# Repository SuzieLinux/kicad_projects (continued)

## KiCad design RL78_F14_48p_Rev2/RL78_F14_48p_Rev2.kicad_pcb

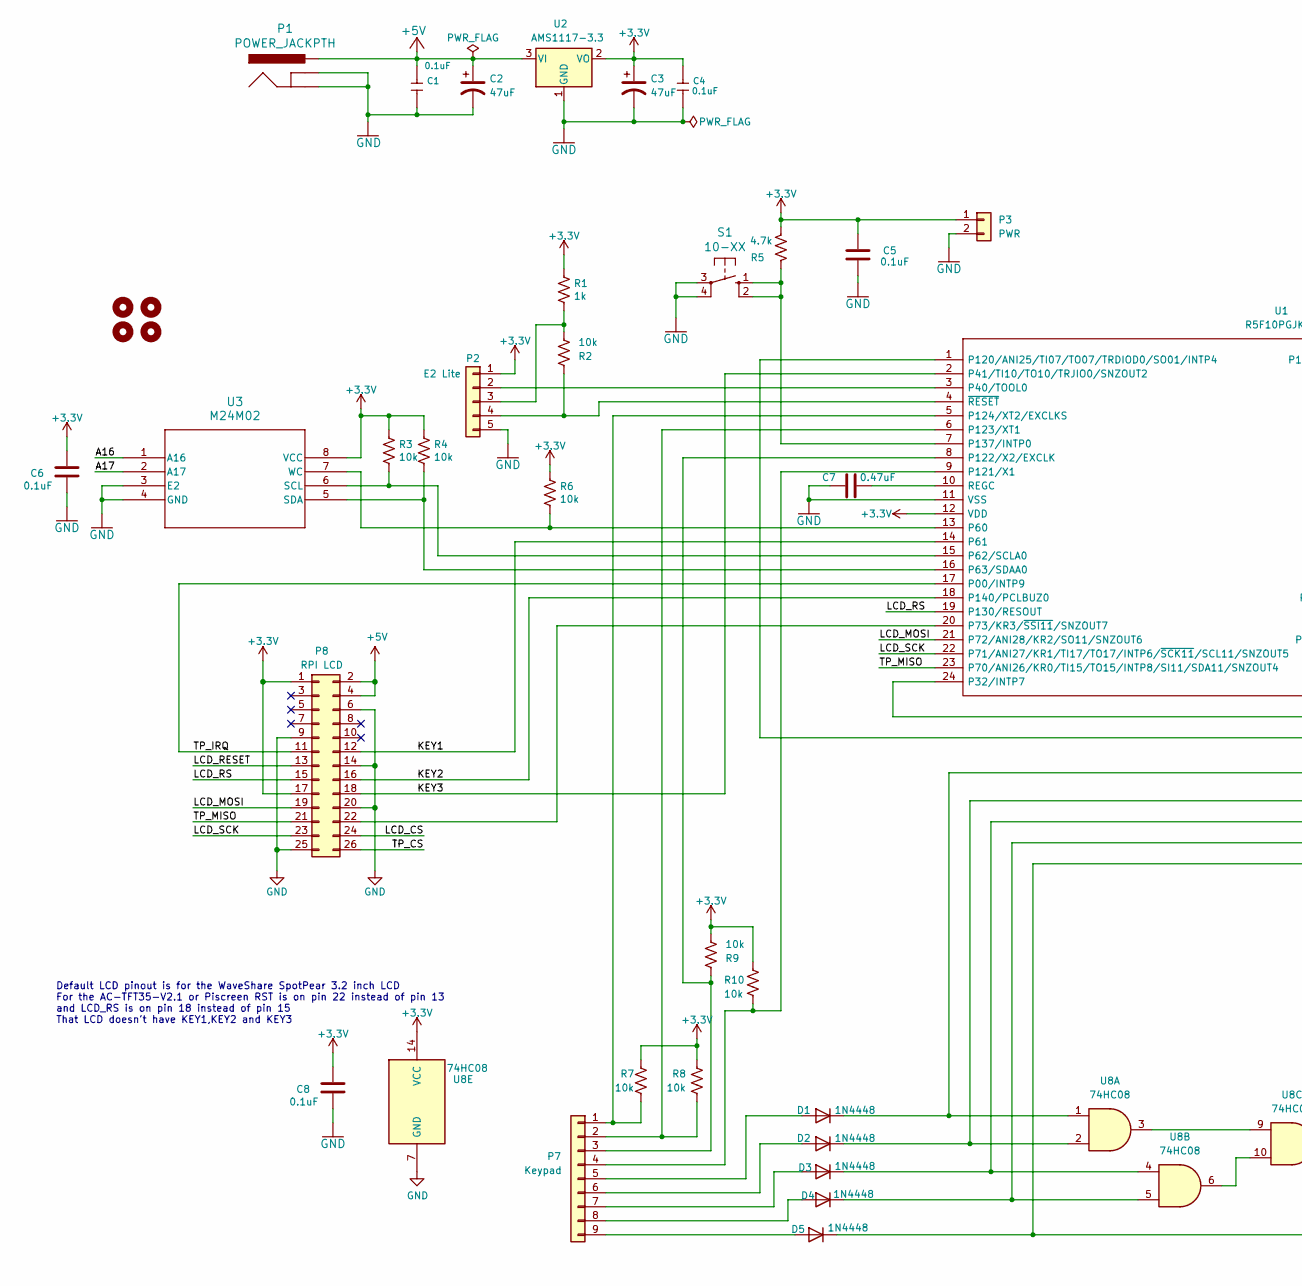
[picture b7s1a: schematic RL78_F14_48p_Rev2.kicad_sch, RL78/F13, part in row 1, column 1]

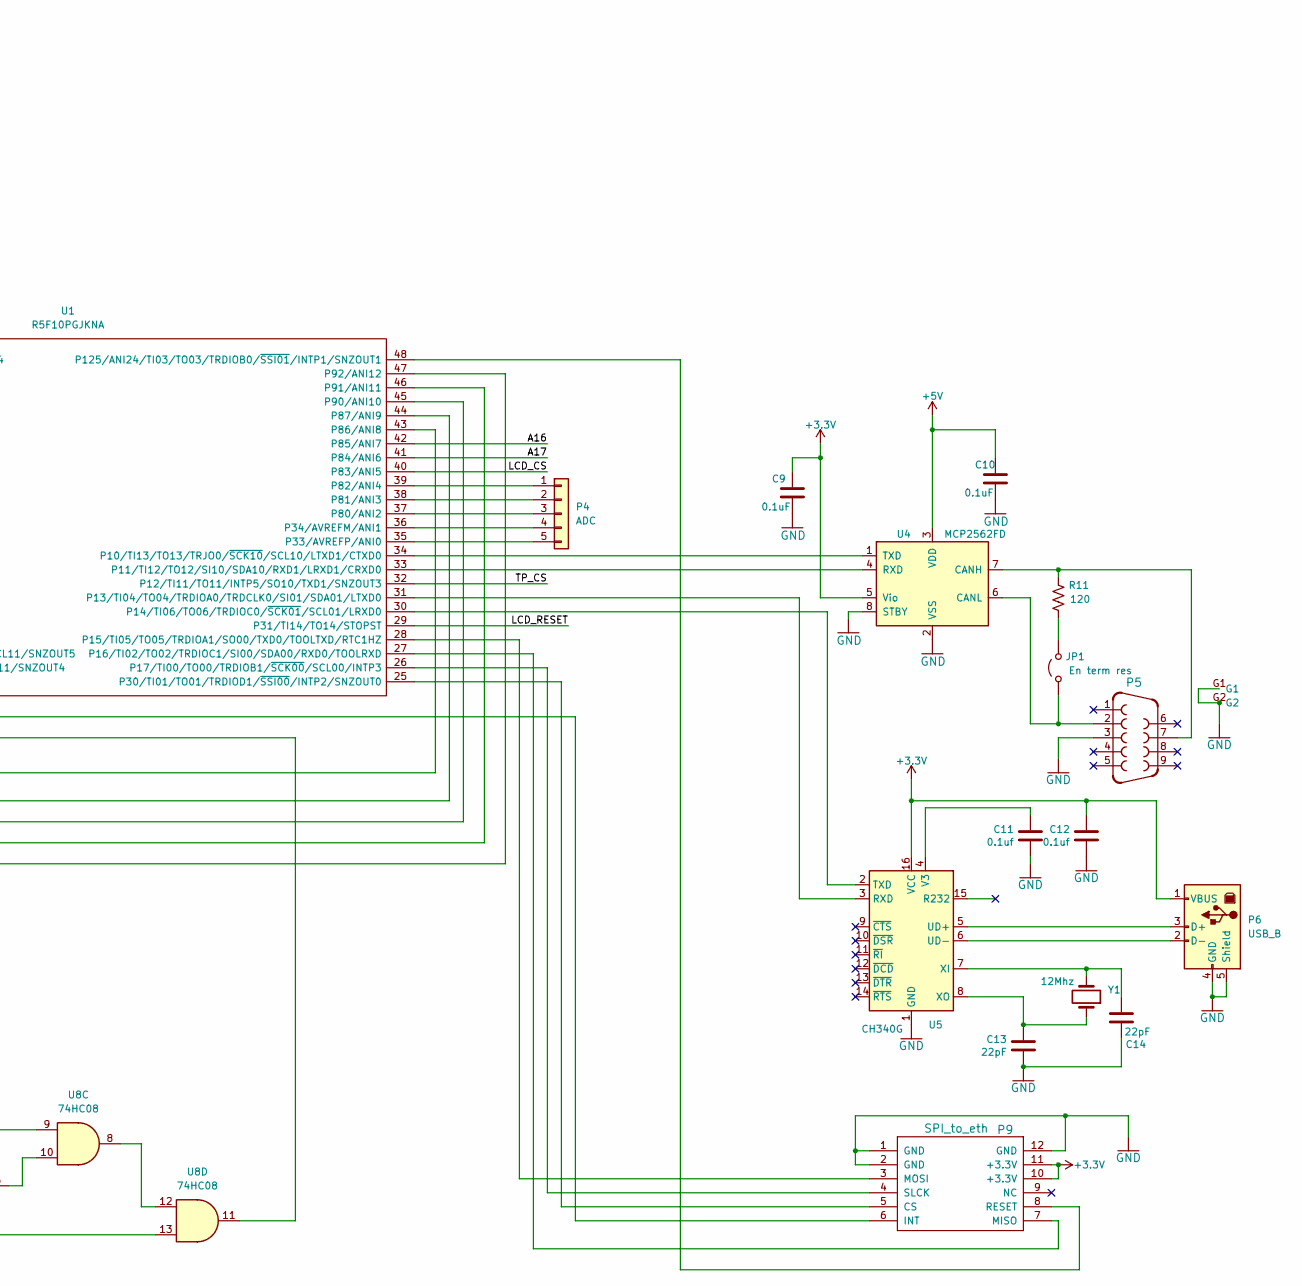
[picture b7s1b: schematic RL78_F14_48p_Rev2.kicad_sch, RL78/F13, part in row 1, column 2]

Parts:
C1, C4: 0.1uF; C_0805_2012Metric_Pad1.18x1.45mm_HandSolder; MPN CC0603KRX7R9BB104; LCSC C14663
C2, C3: 47uF; CP_Radial_D6.3mm_P2.50mm
C5, C6, C8, C9, C10: 0.1uF; C_0805_2012Metric_Pad1.18x1.45mm_HandSolder
C7: 0.47uF; C_0805_2012Metric_Pad1.18x1.45mm_HandSolder
C11, C12: 0.1uf; C_0805_2012Metric_Pad1.18x1.45mm_HandSolder
C13, C14: 22pF; C_0805_2012Metric_Pad1.18x1.45mm_HandSolder
D1, D2, D3, D4, D5: 1N4448; D_DO-35_SOD27_P7.62mm_Horizontal
H1, H2, H3, H4: MountingHole; MountingHole_2.7mm_M2.5_DIN965_Pad
JP1: En term res; PinHeader_1x02_P2.54mm_Vertical
P1: POWER_JACKPTH; POWER_JACK_PTH
P2: E2 Lite; PinHeader_1x05_P2.54mm_Vertical
P3: PWR; PinSocket_1x02_P2.54mm_Vertical
P4: ADC; PinSocket_1x05_P2.00mm_Vertical
P5: F09HP
P6: USB_B; USB_B_OST_USB-B1HSxx_Horizontal
P7: Keypad; PinHeader_1x09_P2.54mm_Vertical
P8: RPI LCD; PinSocket_2x13_P2.54mm_Vertical
P9: SPI_to_eth
R1: 1k; R_0805_2012Metric
R2, R3, R4, R6, R7, R8, R9, R10: 10k; R_0805_2012Metric
R5: 4.7k; R_0805_2012Metric_Pad1.20x1.40mm_HandSolder
R11: 120; R_2512_6332Metric_Pad1.40x3.35mm_HandSolder
S1: 10-XX; B3F-10XX
U1: R5F10PGJKNA; QFN-48-1EP_8x8mm_P0.5mm_EP6.2x6.2mm; Manufacturer_Part_Number R5F10PGJKNA#U5
U2: AMS1117-3.3; SOT-223-3_TabPin2; LCSC C6186
U3: M24M02; SO_RMN6TP_STM
U4: MCP2562FD; DIP-8_W7.62mm
U5: CH340G; SOIC-16_3.9x9.9mm_P1.27mm; LCSC C14267
U8: 74HC08; SOIC-14_3.9x8.7mm_P1.27mm
Y1: 12Mhz; Crystal_HC49-4H_Vertical

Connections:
+3.3V: C3.1, C4.1, C5.1, C6.1, C8.1, C9.1, C12.1, P2.1, P3.1, P6.1 (VBUS), P8.1, P8.17, P9.10 (+3.3V), P9.11 (+3.3V), R1.1, R3.1, R4.1, R5.2, R6.1, R7.1, R8.1, R9.1, R10.1, U1.12 (VDD), U2.2 (VO), U3.8 (VCC), U4.5 (Vio), U5.16 (VCC), U8.14 (VCC)
+5V: C1.1, C2.1, C10.1, P1.PWR, P8.2, P8.4, U2.3 (VI), U4.3 (VDD)
/A16: U1.42 (P85/ANI7), U3.1 (A16)
/A17: U1.41 (P84/ANI6), U3.2 (A17)
/KEY1: P8.12, U1.14 (P61)
/KEY2: P8.16, U1.18 (P140/PCLBUZ0)
/KEY3: P8.18, U1.2 (P41/TI10/TO10/TRJIO0/SNZOUT2)
/LCD_CS: P8.24, U1.40 (P83/ANI5)
/LCD_MOSI: P8.19, U1.21 (P72/ANI28/KR2/SO11/SNZOUT6)
/LCD_RESET: P8.13, U1.29 (P31/TI14/TO14/STOPST)
/LCD_RS: P8.15, U1.19 (P130/RESOUT)
/LCD_SCK: P8.23, U1.22 (P71/ANI27/KR1/TI17/TO17/INTP6/~SCK11/SC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)
/TP_CS: P8.26, U1.32 (P12/TI11/TO11/INTP5/SO10/TXD1/SNZOUT3)
/TP_IRQ: P8.11, U1.17 (P00/INTP9)
/TP_MISO: P8.21, U1.23 (P70/ANI26/KR0/TI15/TO15/INTP8/SI11/SDA1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)
GND: C1.2, C2.2, C3.2, C4.2, C5.2, C6.2, C7.2, C8.2, C9.2, C10.2, C11.2, C12.2, C13.2, C14.2, P1.GND, P1.GNDBREAK, P2.5, P3.2, P5.3, P5.G1, P5.G2, P6.4 (GND), P6.5 (Shield), P8.6, P8.9, P8.14, P8.20, P8.25, P9.1 (GND), P9.2 (GND), P9.12 (GND), S1.3, S1.4 (P1), U1.11 (VSS), U2.1 (GND), U3.3 (E2), U3.4 (GND), U4.2 (VSS), U4.8 (STBY), U5.1 (GND), U8.7 (GND)
unnamed: D1.2 (A), P7.5
unnamed: D1.1 (K), U1.43 (P86/ANI8), U8.1
unnamed: D2.2 (A), P7.6
unnamed: D2.1 (K), U1.44 (P87/ANI9), U8.2
unnamed: D3.2 (A), P7.7
unnamed: D3.1 (K), U1.45 (P90/ANI10), U8.4
unnamed: D4.2 (A), P7.8
unnamed: D4.1 (K), U1.46 (P91/ANI11), U8.5
unnamed: D5.2 (A), P7.9
unnamed: D5.1 (K), U1.47 (P92/ANI12), U8.13
unnamed: JP1.1 (A), P5.2, U4.6 (CANL)
unnamed: JP1.2 (B), R11.2
unnamed: P2.2, U1.3 (P40/TOOL0)
unnamed: P2.3, R1.2, R2.1
unnamed: P2.4, R2.2, U1.4 (~RESET)
unnamed: P4.1, U1.39 (P82/ANI4)
unnamed: P4.2, U1.38 (P81/ANI3)
unnamed: P4.3, U1.37 (P80/ANI2)
unnamed: P4.4, U1.36 (P34/AVREFM/ANI1)
unnamed: P4.5, U1.35 (P33/AVREFP/ANI0)
unnamed: P6.3 (D+), U5.5 (UD+)
unnamed: P6.2 (D-), U5.6 (UD-)
unnamed: P7.1, R7.2, U1.5 (P124/XT2/EXCLKS)
unnamed: P7.2, R8.2, U1.6 (P123/XT1)
unnamed: P7.3, R9.2, U1.8 (P122/X2/EXCLK)
unnamed: P7.4, R10.2, U1.9 (P121/X1)
unnamed: P8.22, U1.20 (P73/KR3/~SSI11/SNZOUT7)
unnamed: P9.5 (CS), U1.25 (P30/TI01/TO01/TRDIOD1/~SSI00/INTP2/SNZO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)
unnamed: P9.6 (INT), U1.24 (P32/INTP7)
unnamed: P9.7 (MISO), U1.27 (P16/TI02/TO02/TRDIOC1/SI00/SDA00/RXD0/T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)
unnamed: P9.3 (MOSI), U1.28 (P15/TI05/TO05/TRDIOA1/SO00/TXD0/TOOLTXD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)
unnamed: P9.8 (RESET), U1.48 (P125/ANI24/TI03/TO03/TRDIOB0/~SSI01/INT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)
unnamed: P9.4 (SLCK), U1.26 (P17/TI00/TO00/TRDIOB1/~SCK00/SCL00/INTP3)
unnamed: R5.1, S1.1 (S), S1.2 (S1), U1.7 (P137/INTP0)
unnamed: U1.34 (P10/TI13/TO13/TRJO0/~SCK10/SCL10/LTXD1/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), U4.1 (TXD)
unnamed: U1.33 (P11/TI12/TO12/SI10/SDA10/RXD1/LRXD1/CRX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), U4.4 (RXD)
unnamed: U1.31 (P13/TI04/TO04/TRDIOA0/TRDCLK0/SI01/SDA0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), U5.3 (RXD)
unnamed: U1.30 (P14/TI06/TO06/TRDIOC0/~SCK01/SCL01/LRXD0), U5.2 (TXD)
unnamed: R6.2, U1.13 (P60), U3.7 (WC)
unnamed: R3.2, U1.15 (P62/SCLA0), U3.6 (SCL)
unnamed: R4.2, U1.16 (P63/SDAA0), U3.5 (SDA)
unnamed: U1.1 (P120/ANI25/TI07/TO07/TRDIOD0/SO01/INTP4), U8.11
unnamed: C7.1, U1.10 (REGC)
unnamed: P5.7, R11.1, U4.7 (CANH)
unnamed: C11.1, U5.4 (V3)
unnamed: C14.1, U5.7 (XI), Y1.2
unnamed: C13.1, U5.8 (XO), Y1.1
unnamed: U8.3, U8.9
unnamed: U8.6, U8.10
unnamed: U8.8, U8.12

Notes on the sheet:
Default LCD pinout is for the WaveShare SpotPear 3.2 inch LCD For the AC-TFT35-V2.1 or Piscreen RST is on pin 22 instead of pin 13 and LCD_RS is on pin 18 instead of pin 15 That LCD doesn't have KEY1,KEY2 and KEY3

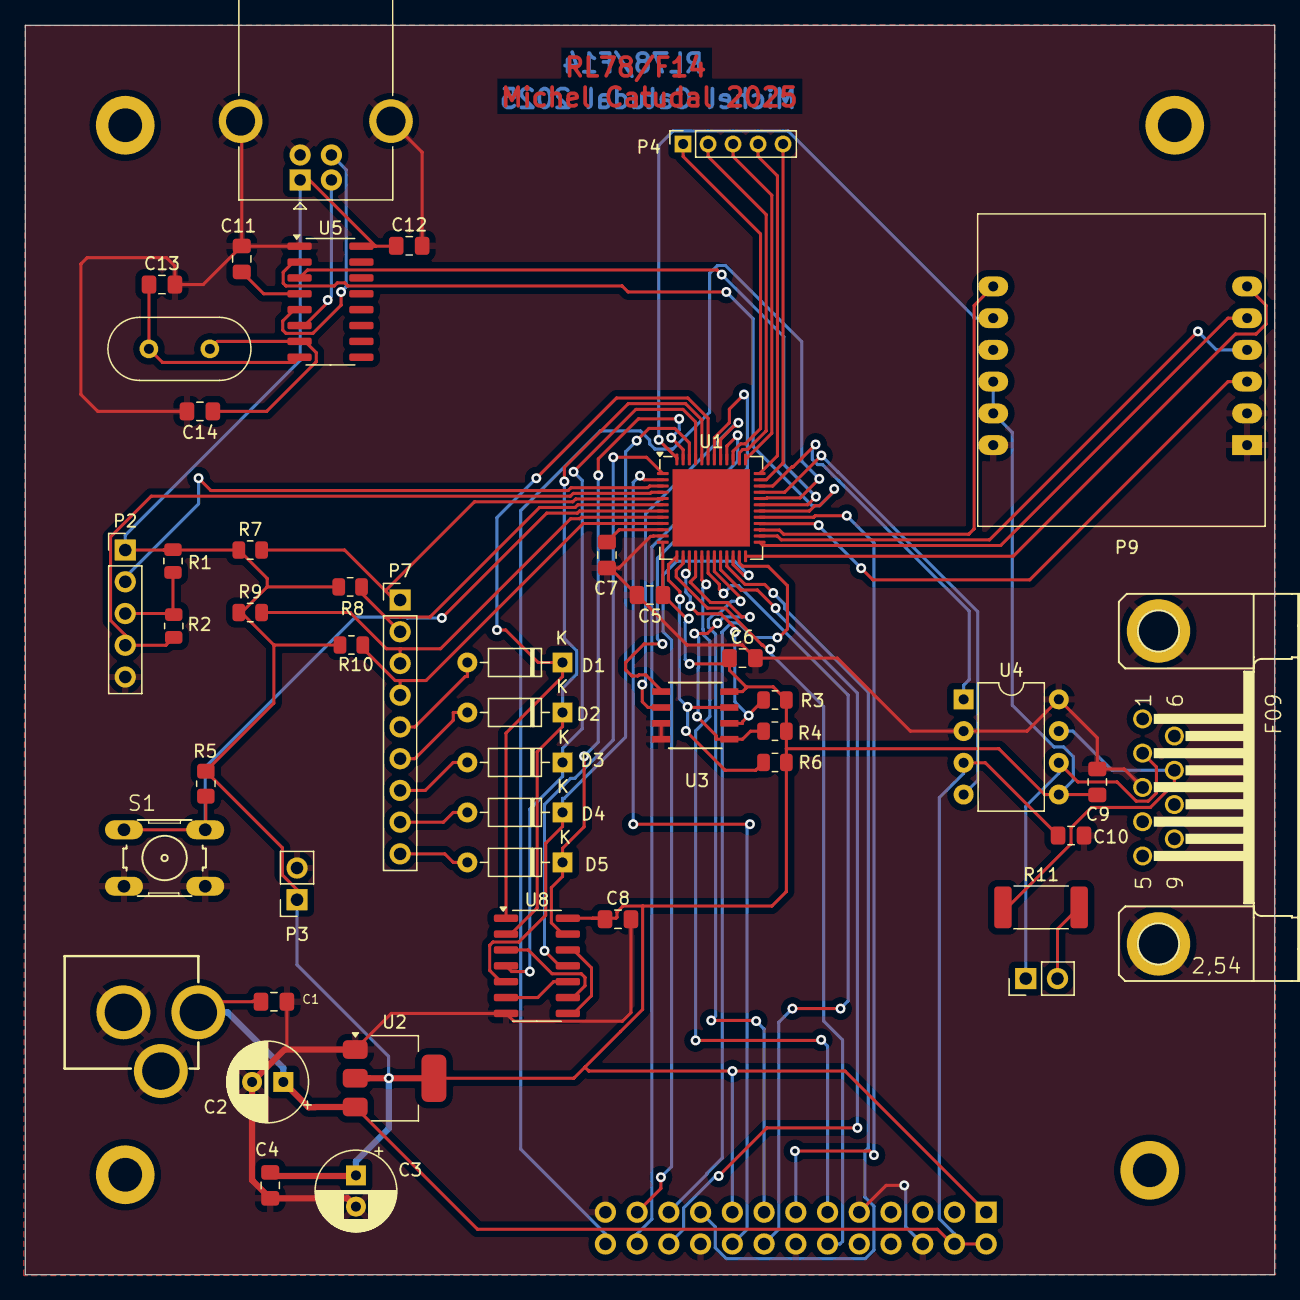
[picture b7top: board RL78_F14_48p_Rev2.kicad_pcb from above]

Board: 2 copper layers, 100.0 x 100.0 mm, 52 parts (1 on the bottom side), 66 nets.
